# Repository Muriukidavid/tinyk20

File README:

Kicad design of the tinyK20 board

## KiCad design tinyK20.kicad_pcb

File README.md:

TinyK20 was an idea by Professor Erich Styger [mcuoneclipse.com] to help students have a board that they can use either as a cheap personal ARM debug probe or a prototyping platform.
This is my own version of TinyK20. It is designed in KiCad and all files are included for manufacturing and further modification. It is opensource.

## Features 
* MK20DX128VLH5 NXP Microcontroller
* USB device mode with a possibility for 5V power supply
* External 5V to 3.3V regulator on bottom side
* 10 pin 1.27mm ARM SWD debug port to program the K20
* 10 pin 1.27mm ARM SWD debug port to program an external target
* 2.54mm Header pins for using with a breakout board
* RTC crystal oscillator
* A reset button
* A user LED

## To be added 
* An SD card socket
* Bootloader and debug Firmware
* Instructions for baremetal bootloader applications

### Current Schematic

### PCB Layout Preview 

A top preview of the ongoing PCB design

A 3D preview of the current design

### BOM
<a href="" rel="BOM">

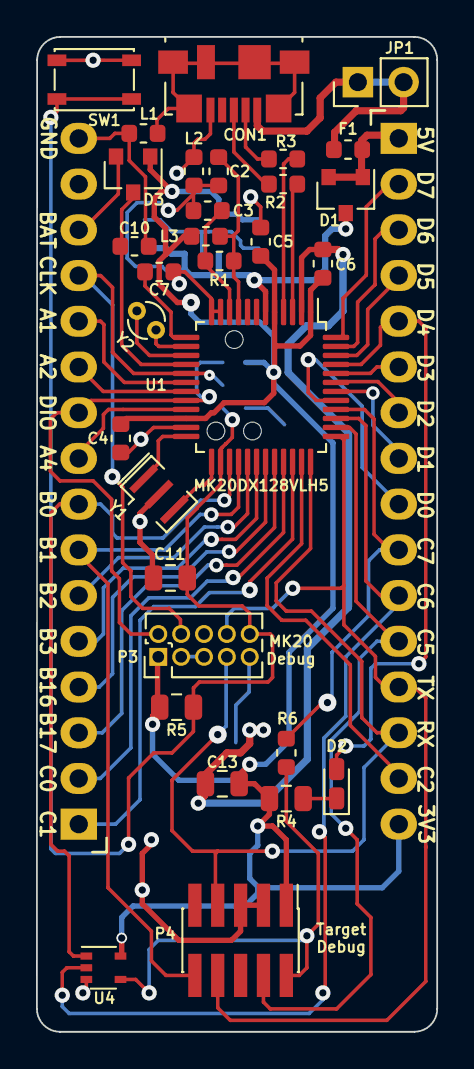
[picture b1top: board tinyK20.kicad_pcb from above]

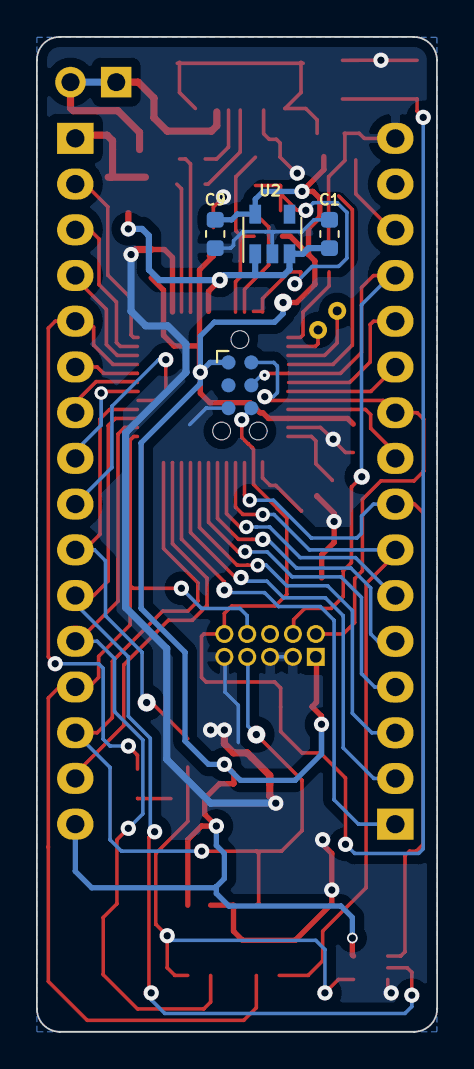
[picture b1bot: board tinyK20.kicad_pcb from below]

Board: 2 copper layers, 22.2 x 55.3 mm, 37 parts (4 on the bottom side), 50 nets.

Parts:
C1, C9: 10uF; C_0603_1608Metric
C2, C6: 2.2u; C_0603_1608Metric
C3, C4, C5, C7: 100n; C_0603_1608Metric
C10: 100nF; C_0603_1608Metric
C11, C13: 100n; C_0805_2012Metric
CON1: USB-MICRO-B; USB_Micro-B_Molex_47346-0001
D1, D3: BAS40-05; SOT-23
D2: LED; LED_0603_1608Metric_Castellated
F1: FUSE_F; Fuse_0603_1608Metric
J2: Conn_02x03_Odd_Even; Tag-Connect_TC2030-IDC-NL_2x03_P1.27mm_Vertical
JP1: JUMPER_F; PinHeader_1x02_P2.54mm_Vertical
L1, L2, L3: INDUCTOR_F; L_0603_1608Metric
P1, P2: CONN_01X16; Pin_Header_Straight_1x16
P3: Debug; PinHeader_2x05_P1.27mm_Vertical
P4: Conn_02x05_Odd_Even; PinHeader_2x05_P1.27mm_Vertical_SMD
R1: 470; R_0603_1608Metric
R2, R3: 33; R_0603_1608Metric
R4: 1K; R_0805_2012Metric
R5: 10K; R_0805_2012Metric
R6: 1k; R_0603_1608Metric
SW1: SW_PUSH; SW_SPST_PTS810
U1: MK20DX128VFT5; LQFP-48_7x7mm_P0.5mm
U2: XC6220B331MR; SOT-23-5
U4: 74AHC1G125; SOT-353_SC-70-5
Y1: 8MHz; Resonator_SMD_muRata_CSTxExxV-3Pin_3.0x1.1mm
Y2: 32.768kHz; Crystal_DS10_D1.0mm_L4.3mm_Vertical

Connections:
3V3: C4.1, C5.1, C6.1, C9.1, C13.1, D3.1, J2.1, L3.2, P2.16, P3.1, P4.1, R4.1, R5.1, U1.1, U1.5, U1.22, U2.5, U4.5
5V: D1.1, D1.2, F1.2, P2.1
/UD+: R2.2, U1.3
/UD-: R3.2, U1.4
/x+: U1.25, Y1.3
/x-: U1.24, Y1.1
D+: CON1.3, R2.1
D-: CON1.2, R3.1
GND: C1.2, C4.2, C5.2, C6.2, C9.2, C10.2, C11.2, C13.2, CON1.5, J2.5, L1.1, L2.1, P1.16, P3.3, P3.5, P3.9, P4.3, P4.5, SW1.1, U1.2, U1.23, U2.2, U4.3, Y1.2
unnamed: C2.1, L3.1, R1.1, U1.9
unnamed: C2.2, C3.2, C7.1, L2.2, U1.11, U1.12
unnamed: C3.1, R1.2, U1.10
unnamed: C7.2, U1.13
unnamed: C10.1, D3.3, U1.16
unnamed: CON1.6, L1.2
unnamed: D2.1, R4.2
unnamed: U1.14, Y2.1
unnamed: U1.15, Y2.2
PTA1: P1.12, U1.18
PTA2: P1.11, U1.19
PTA4: P1.9, U1.21
PTB0: P1.8, U1.27, U4.1
PTB1: P1.7, P4.10, U1.28
PTB2: P1.6, U1.29
PTB3: P1.5, U1.30
PTB16: P1.4, U1.31
PTB17: P1.3, U1.32
PTC0: P1.2, U1.33
PTC1: P1.1, U1.34
PTC2: P2.15, U1.35
PTC5: P2.12, P4.4, U1.38
PTC6: P2.11, U1.39, U4.2
PTC7: P2.10, R6.1, U1.40
PTD0: P2.9, U1.41
PTD1: P2.8, U1.42
PTD2: P2.7, U1.43
PTD3: P2.6, U1.44
PTD4: D2.2, P2.5, U1.45
PTD5: P2.4, U1.46
PTD6: P2.3, U1.47
PTD7: P2.2, U1.48
RESET: C11.1, J2.6, P3.10, R5.2, SW1.2, U1.26
SWD_CLK: J2.4, P1.13, P3.4, U1.17
SWD_IO: J2.2, P1.10, P3.2, U1.20
TGT_SWD_IO: P4.2, R6.2, U4.4
UART1_RX: P2.14, P3.7, P4.7, U1.36
UART1_TX: P2.13, P3.8, P4.8, U1.37
VBATT: D3.2, P1.14
Vreg: CON1.1, F1.1, JP1.1, JP1.2
Vregin: C1.1, D1.3, U1.6, U2.1, U2.3

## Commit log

2016-03-01 Add Initial Schematic Capture
    Add the initial schematic design with all the components, without pcb footprints
2016-03-15 Add pcb layout
    Associate components with their footprints
    Place components in the layout
    Route signals by hand, not yet done
    Create a documents folder to clean up a bit
    Use hand-drilling and hand-soldering headers footprints
2016-06-22 Simplify the board
    Remove all breakout pin headers
    remove SD card connector
    redo the PCB layout
    change the debug connector to through hole 1.27mm
    change the resistor footprints to handsoldering ones
2017-02-07 Add breakout headers and reroute the whole PCB board
2017-02-15 Make the board smaller
    Switch the ABM2 crystal with a smaller Murata CSTE
    Switch the debug line driver chip with a smaller footprint one
    Adjust pin headers hopefully to breadboard friendly
    Remove Jumpers on UART lines
    Remove the 1Mohm resistor and two capacitors for the crystal. Not needed
    Resize the entire board downwards and re-route the traces
2020-07-23 Refresh the project with latest KiCad
    Refresh the schematic and reorganize the placement of components adding a plug of nails optional debug port
    Redo the PCB playout: round corners, update the footprints with latest available from KiCad libraries, add silk screen lables for header pins
    Add a README file with screenshot images of the schematic and PCB layout top and board 3D view
    Add some missing 3D files for fuse and pushbutton
    Change the 3.3V regulator with a smaller package
2020-07-23 Remove obsolete files
